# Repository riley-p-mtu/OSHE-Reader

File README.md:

# OSHE-Reader
This project is a work-in-progress in making an open-source E-ink display E-reader. The intention is to read and display EPUB and PDF files, the most popular book formats.

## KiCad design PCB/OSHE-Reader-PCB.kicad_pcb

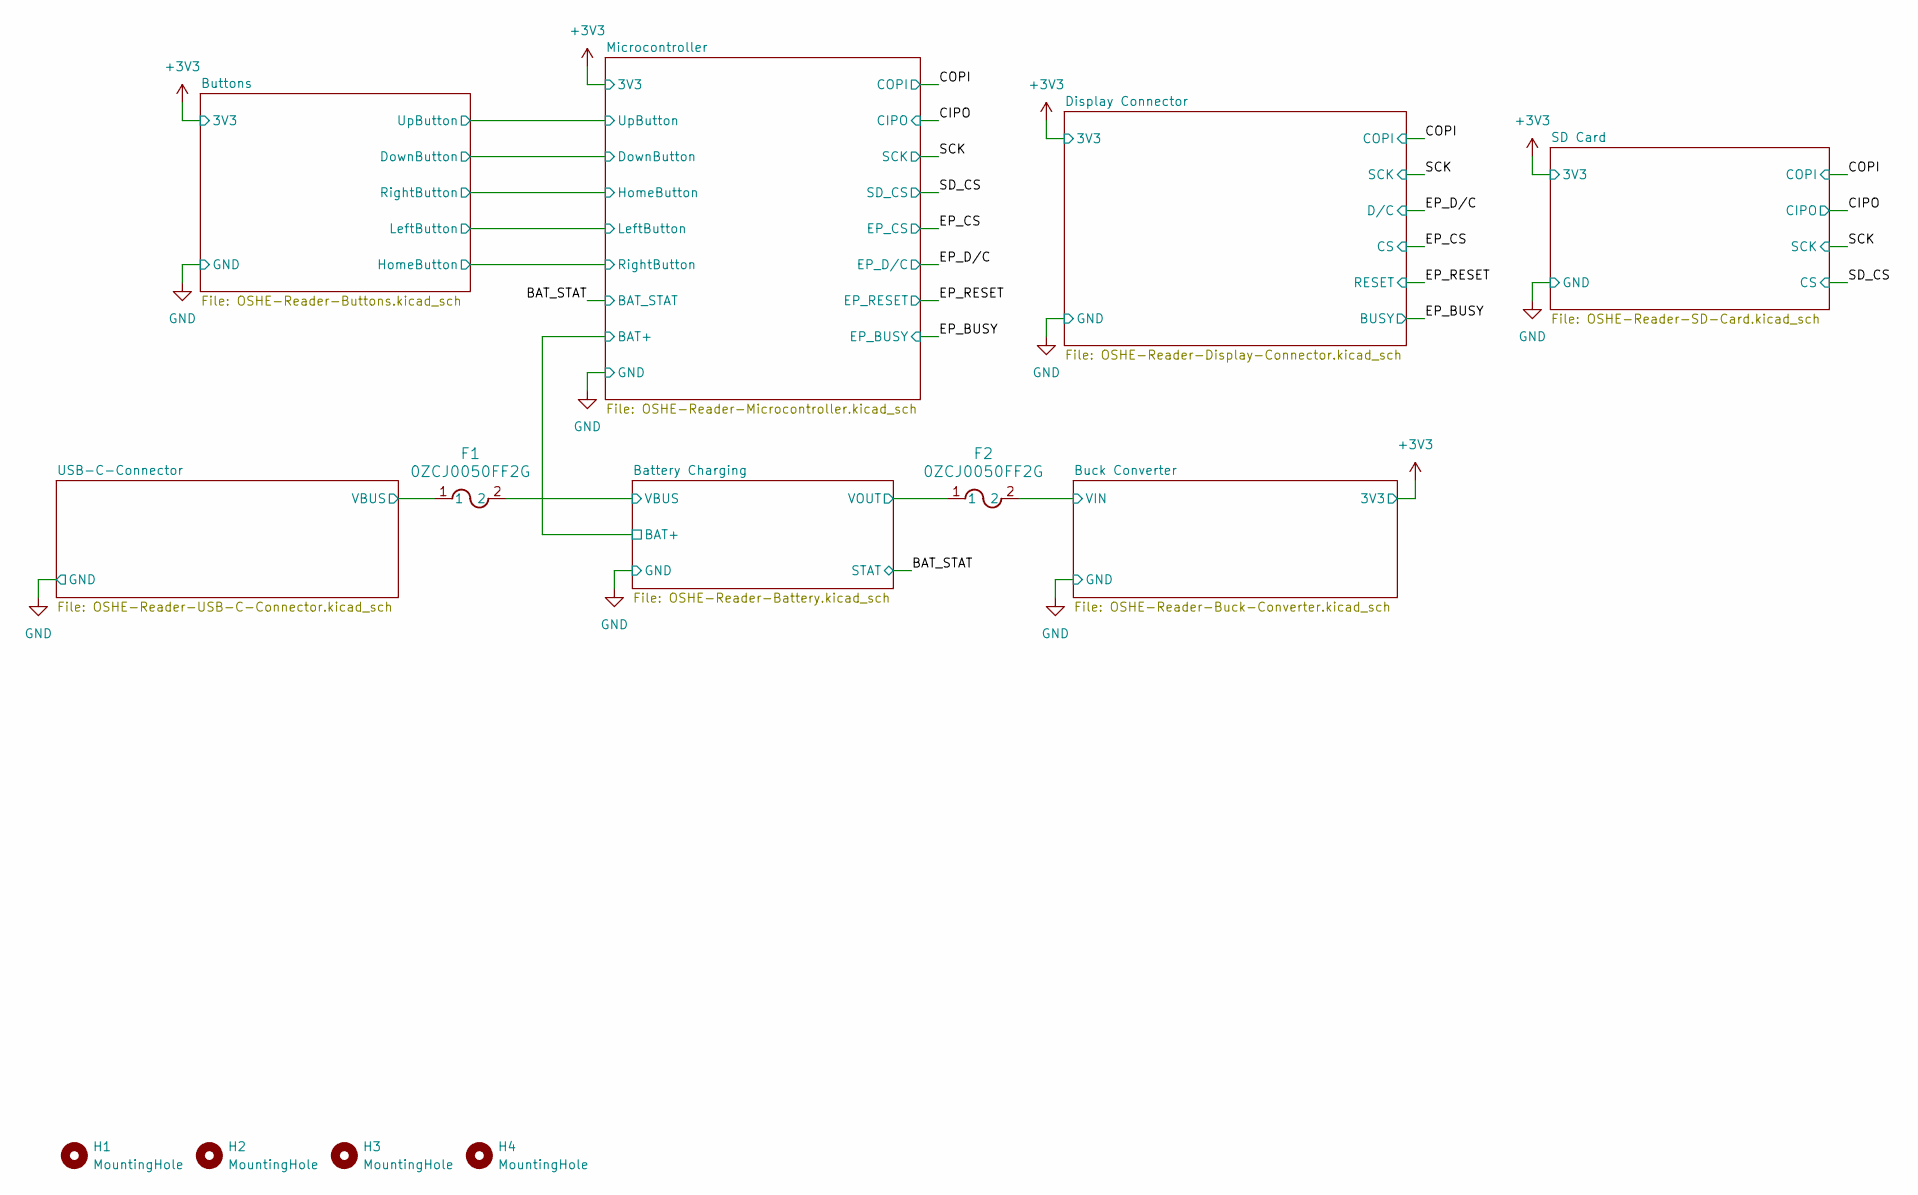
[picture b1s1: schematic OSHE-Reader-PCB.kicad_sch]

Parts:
F1, F2: 0ZCJ0050FF2G; 0ZCJ_BEL
H1, H2, H3, H4: MountingHole; MountingHole_3.2mm_M3

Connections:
/Battery Charging/VBUS: F1.2; also elsewhere on the board
/Battery Charging/VOUT: F2.1; also elsewhere on the board
/Buck Converter/VIN: F2.2; also elsewhere on the board
/USB-C-Connector/VBUS: F1.1; also elsewhere on the board

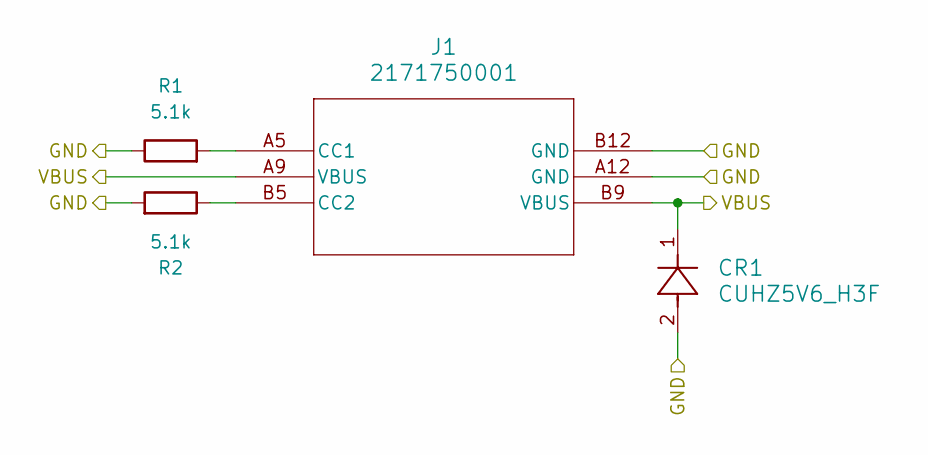
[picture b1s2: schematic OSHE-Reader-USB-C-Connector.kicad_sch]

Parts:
CR1: CUHZ5V6_H3F; SOD-323HEUS2H_TOS
J1: 2171750001; 2171750001_MOL
R1, R2: 5.1k; R_1206_3216Metric

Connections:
/USB-C-Connector/VBUS: CR1.1, J1.A9 (VBUS), J1.B9 (VBUS); also elsewhere on the board
GND: CR1.2, J1.A12 (GND), J1.B12 (GND), R1.1, R2.2; also elsewhere on the board
unnamed: J1.A5 (CC1), R1.2
unnamed: J1.B5 (CC2), R2.1

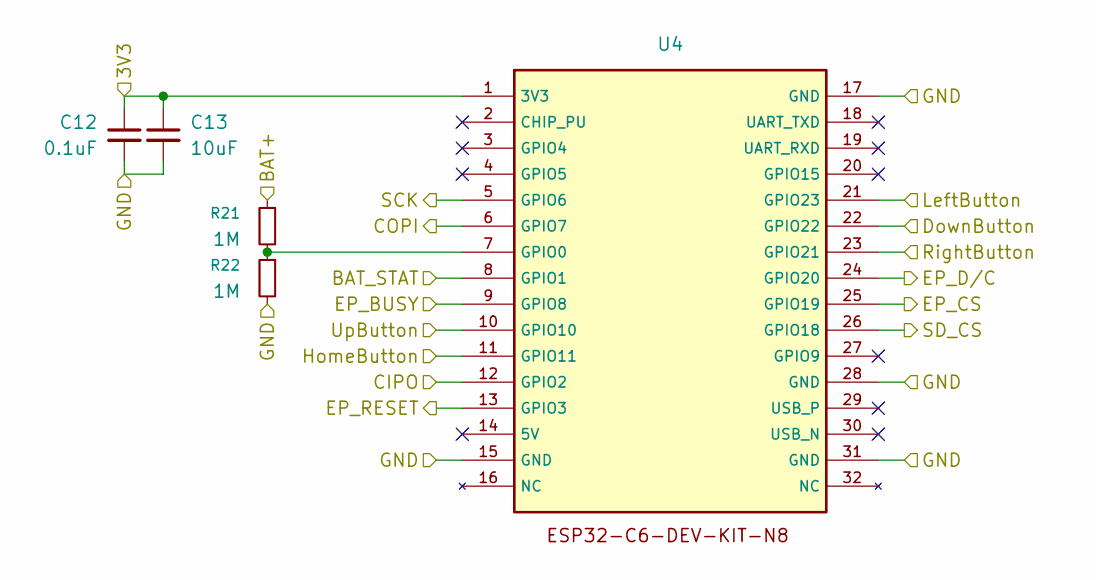
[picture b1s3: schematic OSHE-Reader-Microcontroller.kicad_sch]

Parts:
C12: 0.1uF; C_1206_3216Metric
C13: 10uF; C_1206_3216Metric
R21, R22: 1M; R_1206_3216Metric
U4: ESP32-C6-DEV-KIT-N8

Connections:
+3V3: C12.1, C13.1, U4.1 (3V3); also elsewhere on the board
/BAT_STAT: U4.8 (GPIO1); also elsewhere on the board
/Battery Charging/BAT+: R21.1; also elsewhere on the board
/Buttons/DownButton: U4.22 (GPIO22); also elsewhere on the board
/Buttons/HomeButton: U4.23 (GPIO21); also elsewhere on the board
/Buttons/LeftButton: U4.21 (GPIO23); also elsewhere on the board
/Buttons/RightButton: U4.11 (GPIO11); also elsewhere on the board
/Buttons/UpButton: U4.10 (GPIO10); also elsewhere on the board
/CIPO: U4.12 (GPIO2); also elsewhere on the board
/COPI: U4.6 (GPIO7); also elsewhere on the board
/EP_BUSY: U4.9 (GPIO8); also elsewhere on the board
/EP_CS: U4.25 (GPIO19); also elsewhere on the board
/EP_D/C: U4.24 (GPIO20); also elsewhere on the board
/EP_RESET: U4.13 (GPIO3); also elsewhere on the board
/SCK: U4.5 (GPIO6); also elsewhere on the board
/SD_CS: U4.26 (GPIO18); also elsewhere on the board
GND: C12.2, C13.2, R22.2, U4.15 (GND), U4.17 (GND), U4.28 (GND), U4.31 (GND); also elsewhere on the board
unnamed: R21.2, R22.1, U4.7 (GPIO0)

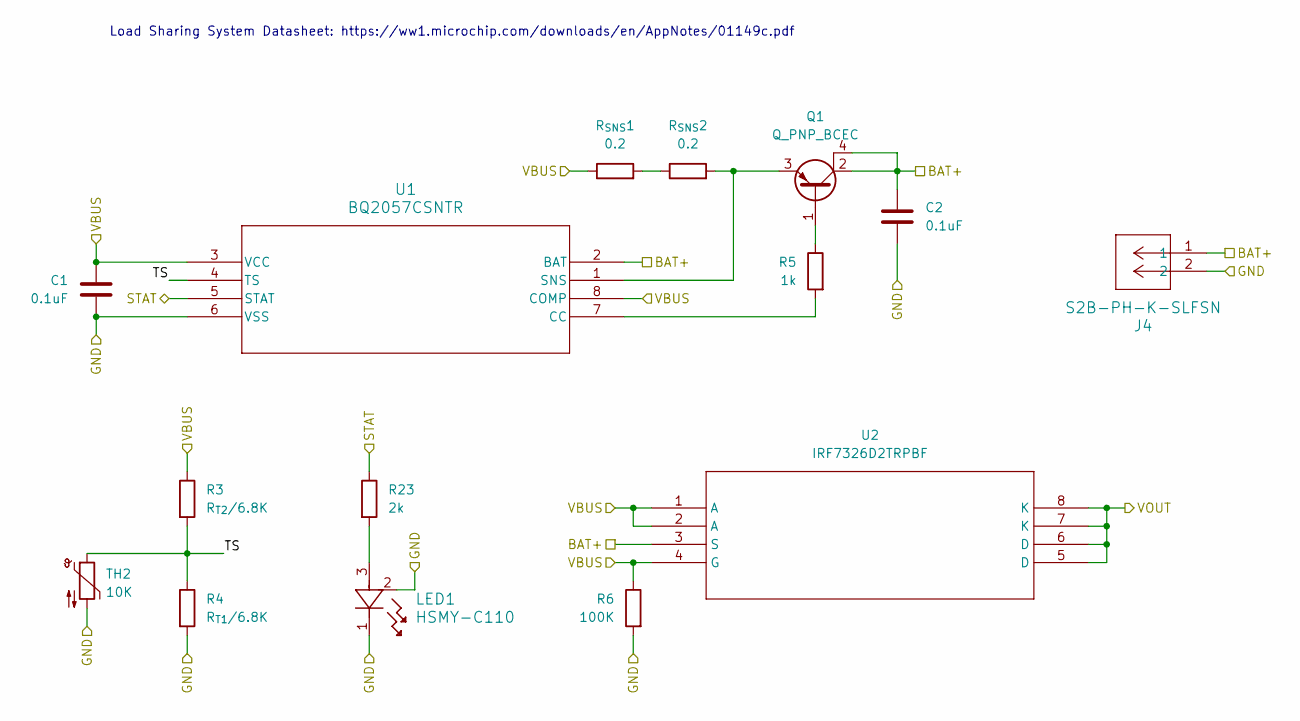
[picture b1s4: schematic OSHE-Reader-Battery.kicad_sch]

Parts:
C1, C2: 0.1uF; C_1206_3216Metric
J4: S2B-PH-K-SLFSN; CONN_S2B-PH-K-S_JST
LED1: HSMY-C110; LED3_HSMx-C110_AVA
Q1: Q_PNP_BCEC; SOT-223
R3: R_{T2}/6.8K; R_1206_3216Metric
R4: R_{T1}/6.8K; R_1206_3216Metric
R5: 1k; R_1206_3216Metric
R6: 100K; R_1206_3216Metric
R23: 2k; R_1206_3216Metric
R_{SNS}1, R_{SNS}2: 0.2; RES_2512_WSL
TH2: 10K; R_Axial_DIN0204_L3.6mm_D1.6mm_P5.08mm_Vertical
U1: BQ2057CSNTR; D8
U2: IRF7326D2TRPBF; SO-8_3.9x4.9mm_P1.27mm

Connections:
/BAT_STAT: R23.1, U1.5 (STAT); also elsewhere on the board
/Battery Charging/BAT+: C2.1, J4.1, Q1.2 (C), Q1.4 (C), U1.2 (BAT), U2.3 (S); also elsewhere on the board
/Battery Charging/TS: R3.2, R4.1, TH2.1, U1.4 (TS)
/Battery Charging/VBUS: C1.1, R3.1, R6.1, R_{SNS}1.1, U1.3 (VCC), U1.8 (COMP), U2.1 (A), U2.2 (A), U2.4 (G); also elsewhere on the board
/Battery Charging/VOUT: U2.5 (D), U2.6 (D), U2.7 (K), U2.8 (K); also elsewhere on the board
GND: C1.2, C2.2, J4.2, LED1.1, LED1.2, R4.2, R6.2, TH2.2, U1.6 (VSS); also elsewhere on the board
unnamed: LED1.3, R23.2
unnamed: Q1.1 (B), R5.1
unnamed: Q1.3 (E), R_{SNS}2.2, U1.1 (SNS)
unnamed: R_{SNS}1.2, R_{SNS}2.1
unnamed: R5.2, U1.7 (CC)

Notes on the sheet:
Load Sharing System Datasheet: https://ww1.microchip.com/downloads/en/AppNotes/01149c.pdf

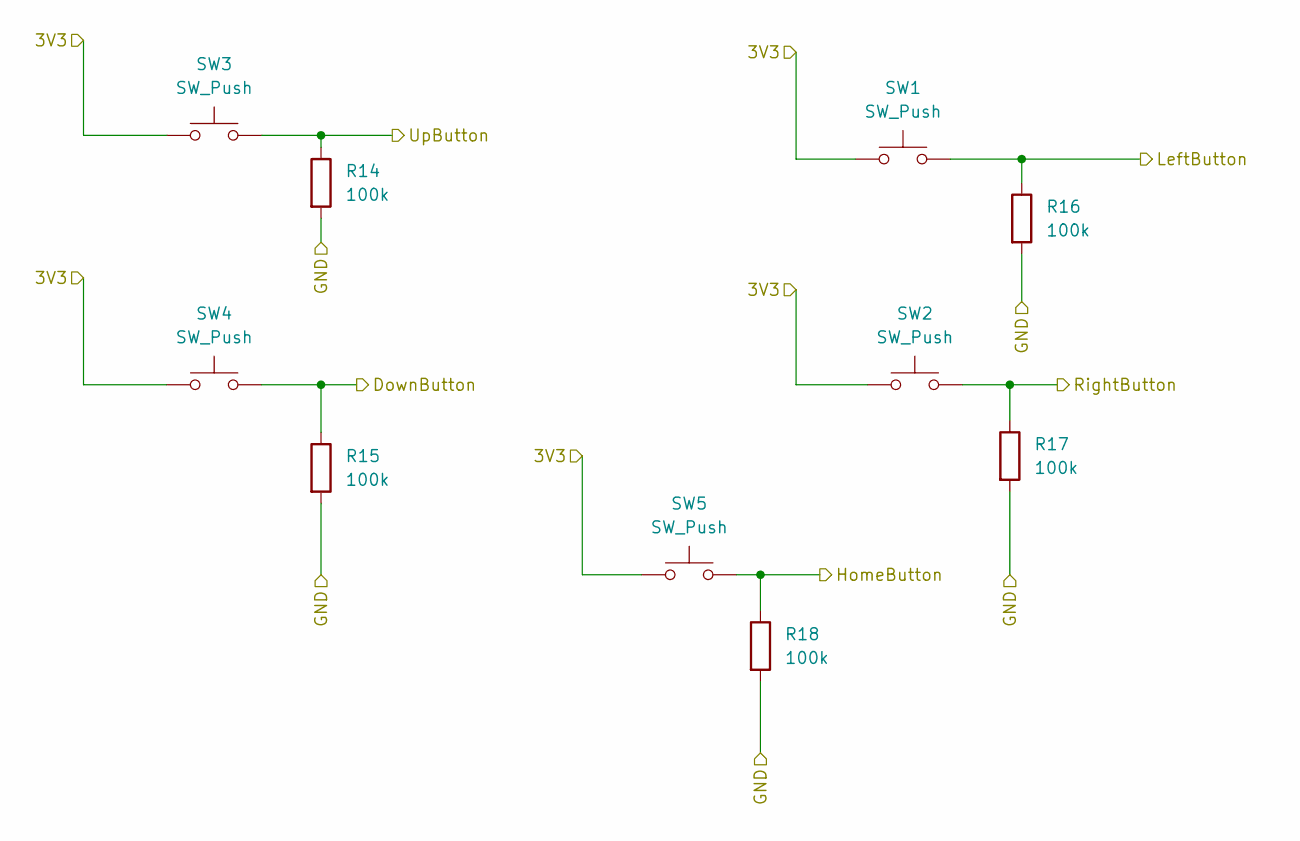
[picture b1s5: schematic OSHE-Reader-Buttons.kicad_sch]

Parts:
R14, R15, R16, R17, R18: 100k; R_1206_3216Metric
SW1, SW2, SW3, SW4, SW5: SW_Push; SW_Tactile_SPST_NO_Straight_CK_PTS636Sx25SMTRLFS

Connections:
+3V3: SW1.2, SW2.1, SW3.1, SW4.1, SW5.1; also elsewhere on the board
/Buttons/DownButton: R15.1, SW4.2; also elsewhere on the board
/Buttons/HomeButton: R18.1, SW5.2; also elsewhere on the board
/Buttons/LeftButton: R16.1, SW1.1; also elsewhere on the board
/Buttons/RightButton: R17.1, SW2.2; also elsewhere on the board
/Buttons/UpButton: R14.1, SW3.2; also elsewhere on the board
GND: R14.2, R15.2, R16.2, R17.2, R18.2; also elsewhere on the board

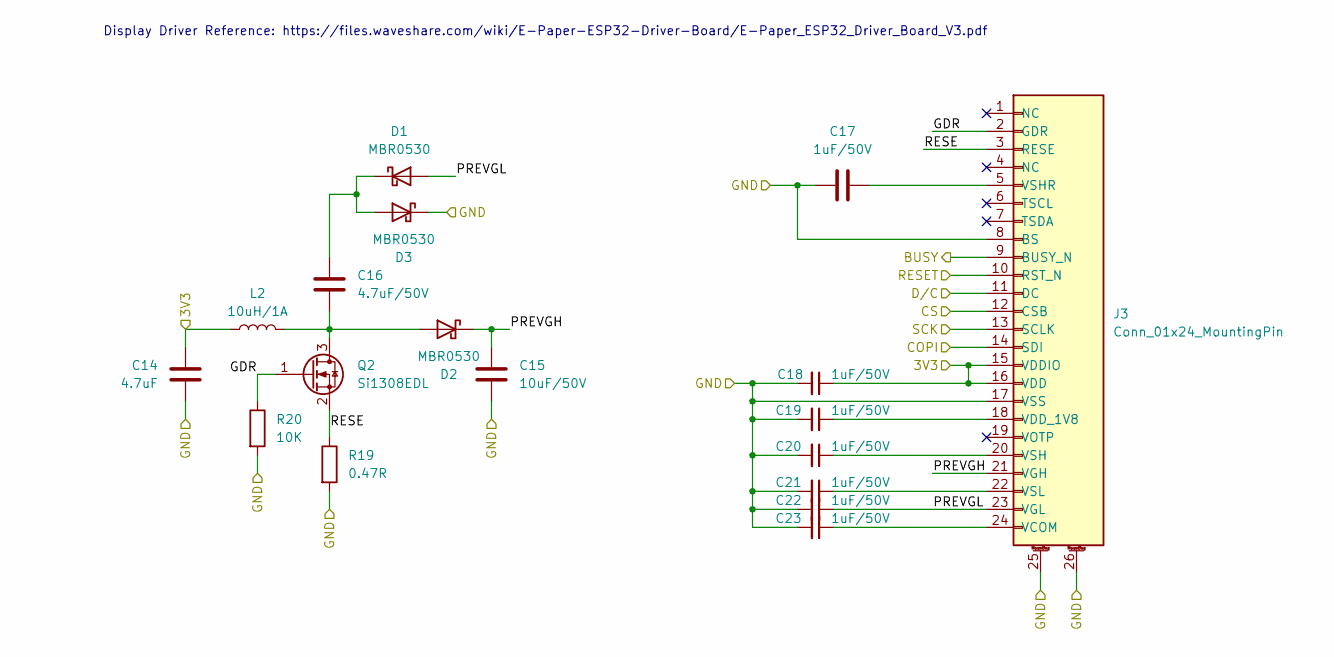
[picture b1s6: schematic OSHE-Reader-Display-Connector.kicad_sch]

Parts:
C14: 4.7uF; C_1206_3216Metric
C15: 10uF/50V; C_1206_3216Metric
C16: 4.7uF/50V; C_1206_3216Metric
C17, C18, C19, C20, C21, C22, C23: 1uF/50V; C_1206_3216Metric
D1, D2, D3: MBR0530; D_SOD-123
J3: Conn_01x24_MountingPin; CONN24_1X24_DRC_FFC_HIR
L2: 10uH/1A; L_1812_4532Metric
Q2: Si1308EDL; SOT-323_SC-70
R19: 0.47R; R_1206_3216Metric
R20: 10K; R_1206_3216Metric

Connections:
+3V3: C14.1, C18.1, J3.15 (VDDIO), J3.16 (VDD), L2.1; also elsewhere on the board
/COPI: J3.14 (SDI); also elsewhere on the board
/Display Connector/GDR: J3.2 (GDR), Q2.1 (G), R20.1
/Display Connector/PREVGH: C15.1, D2.1 (K), J3.21 (VGH)
/Display Connector/PREVGL: C22.1, D1.2 (A), J3.23 (VGL)
/Display Connector/RESE: J3.3 (RESE), Q2.2 (S), R19.1
/EP_BUSY: J3.9 (BUSY_N); also elsewhere on the board
/EP_CS: J3.12 (CSB); also elsewhere on the board
/EP_D/C: J3.11 (DC); also elsewhere on the board
/EP_RESET: J3.10 (RST_N); also elsewhere on the board
/SCK: J3.13 (SCLK); also elsewhere on the board
GND: C14.2, C15.2, C17.2, C18.2, C19.2, C20.2, C21.2, C22.2, C23.2, D3.1 (K), J3.8 (BS), J3.17 (VSS), J3.25, J3.26, R19.2, R20.2; also elsewhere on the board
unnamed: C16.1, D1.1 (K), D3.2 (A)
unnamed: C16.2, D2.2 (A), L2.2, Q2.3 (D)
unnamed: C23.1, J3.24 (VCOM)
unnamed: C19.1, J3.18 (VDD_1V8)
unnamed: C20.1, J3.20 (VSH)
unnamed: C17.1, J3.5 (VSHR)
unnamed: C21.1, J3.22 (VSL)

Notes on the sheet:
Display Driver Reference: https://files.waveshare.com/wiki/E-Paper-ESP32-Driver-Board/E-Paper_ESP32_Driver_Board_V3.pdf

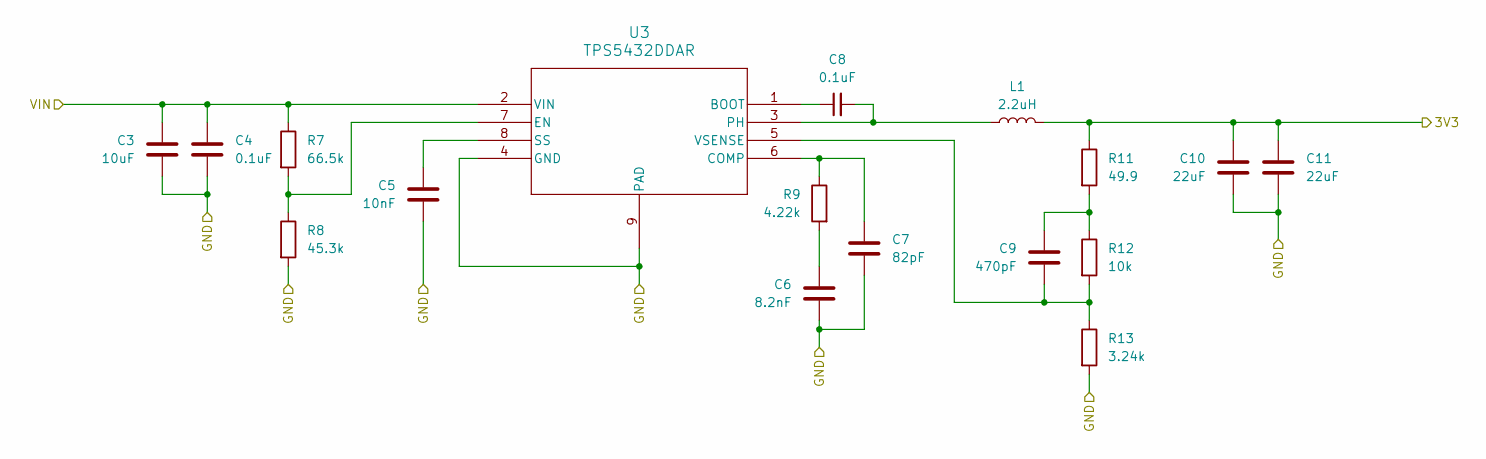
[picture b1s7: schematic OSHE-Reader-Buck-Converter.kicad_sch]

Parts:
C3: 10uF; C_1206_3216Metric
C4, C8: 0.1uF; C_1206_3216Metric
C5: 10nF; C_1206_3216Metric
C6: 8.2nF; C_1206_3216Metric
C7: 82pF; C_1206_3216Metric
C9: 470pF; C_1206_3216Metric
C10, C11: 22uF; C_1206_3216Metric
L1: 2.2uH; L_1206_3216Metric
R7: 66.5k; R_1206_3216Metric
R8: 45.3k; R_1206_3216Metric
R9: 4.22k; R_1206_3216Metric
R11: 49.9; R_1206_3216Metric
R12: 10k; R_1206_3216Metric
R13: 3.24k; R_1206_3216Metric
U3: TPS5432DDAR; DDA_R-PDSO-G8_TEX

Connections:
+3V3: C10.2, C11.2, L1.2, R11.1; also elsewhere on the board
/Buck Converter/VIN: C3.1, C4.1, R7.1, U3.2 (VIN); also elsewhere on the board
GND: C3.2, C4.2, C5.2, C6.2, C7.2, C10.1, C11.1, R8.2, R13.2, U3.4 (GND), U3.9 (PAD); also elsewhere on the board
unnamed: C6.1, R9.2
unnamed: C9.2, R11.2, R12.1
unnamed: C8.1, U3.1 (BOOT)
unnamed: C7.1, R9.1, U3.6 (COMP)
unnamed: R7.2, R8.1, U3.7 (EN)
unnamed: C8.2, L1.1, U3.3 (PH)
unnamed: C5.1, U3.8 (SS)
unnamed: C9.1, R12.2, R13.1, U3.5 (VSENSE)

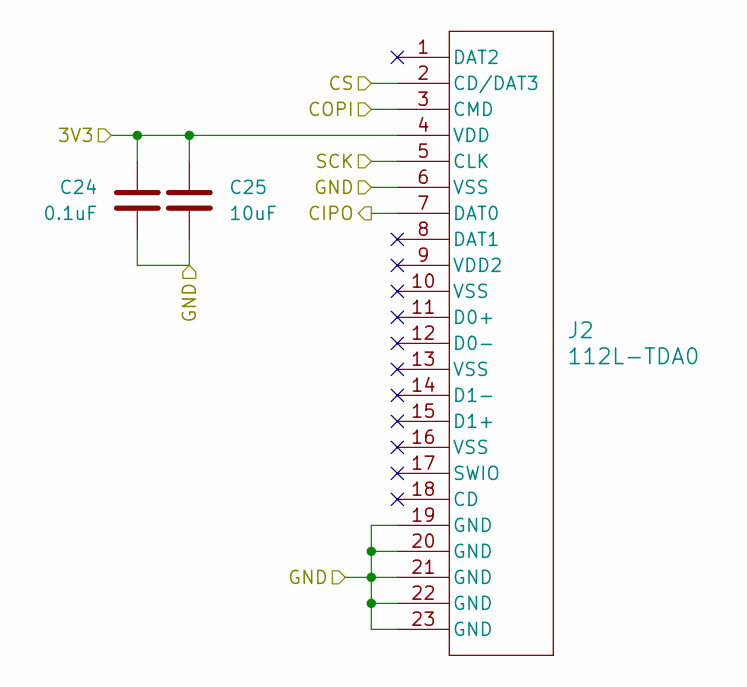
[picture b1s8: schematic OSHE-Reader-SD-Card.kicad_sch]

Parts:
C24: 0.1uF; C_1206_3216Metric
C25: 10uF; C_1206_3216Metric
J2: 112L-TDA0; CONN_112L-TDA0_ATT

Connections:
+3V3: C24.1, C25.1, J2.4 (VDD); also elsewhere on the board
/CIPO: J2.7 (DAT0); also elsewhere on the board
/COPI: J2.3 (CMD); also elsewhere on the board
/SCK: J2.5 (CLK); also elsewhere on the board
/SD_CS: J2.2 (CD/DAT3); also elsewhere on the board
GND: C24.2, C25.2, J2.6 (VSS), J2.19 (GND), J2.20 (GND), J2.21 (GND), J2.22 (GND), J2.23 (GND); also elsewhere on the board

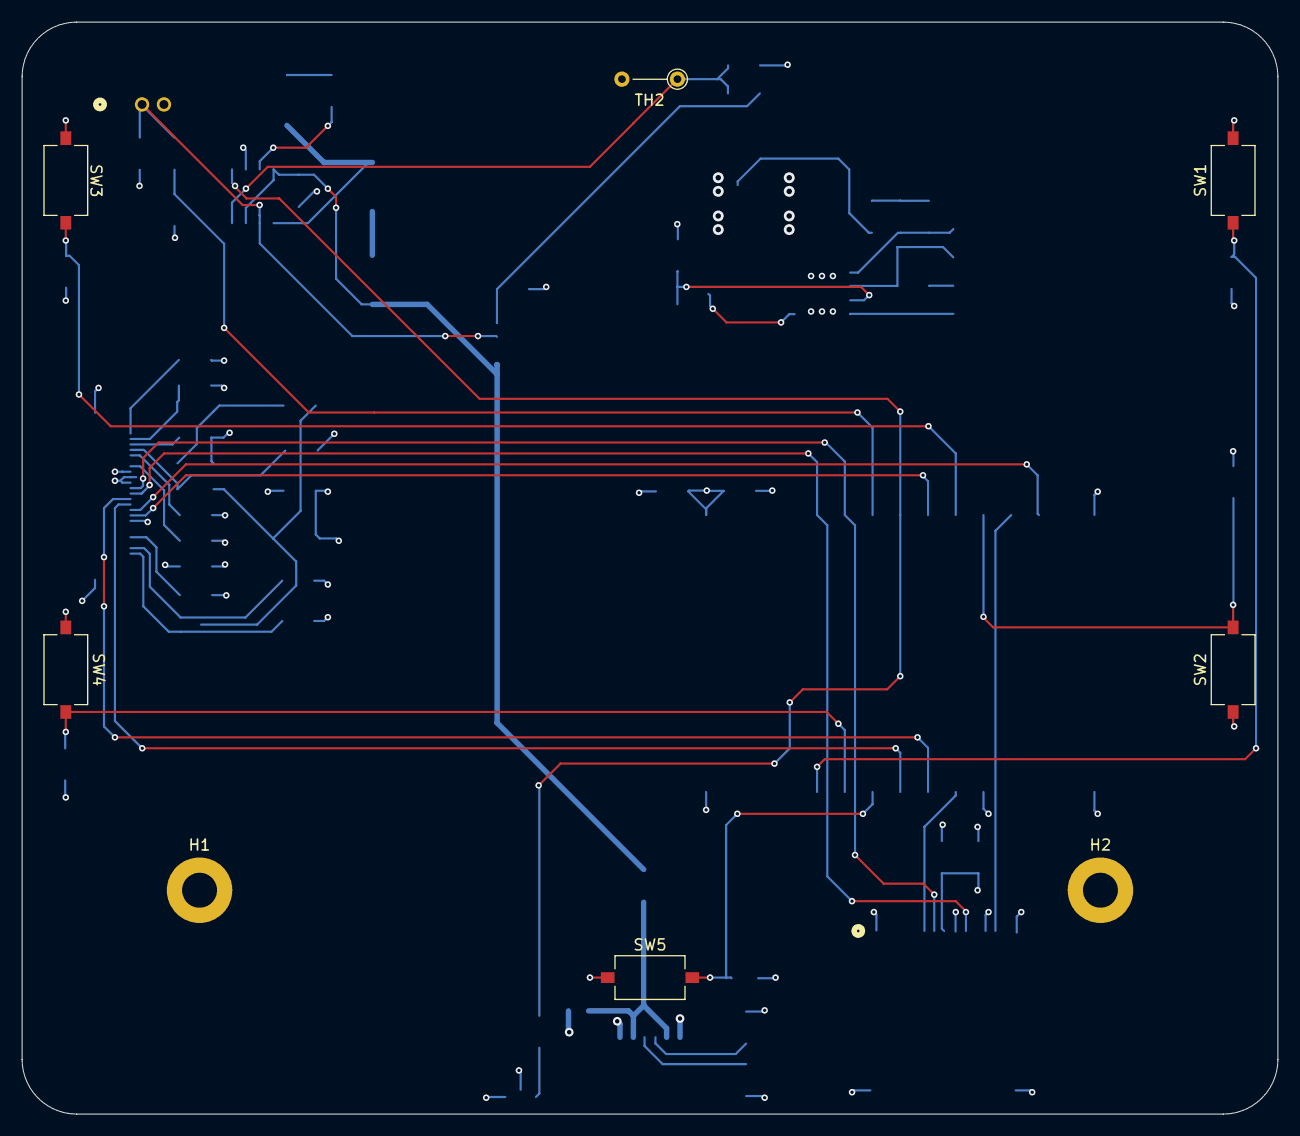
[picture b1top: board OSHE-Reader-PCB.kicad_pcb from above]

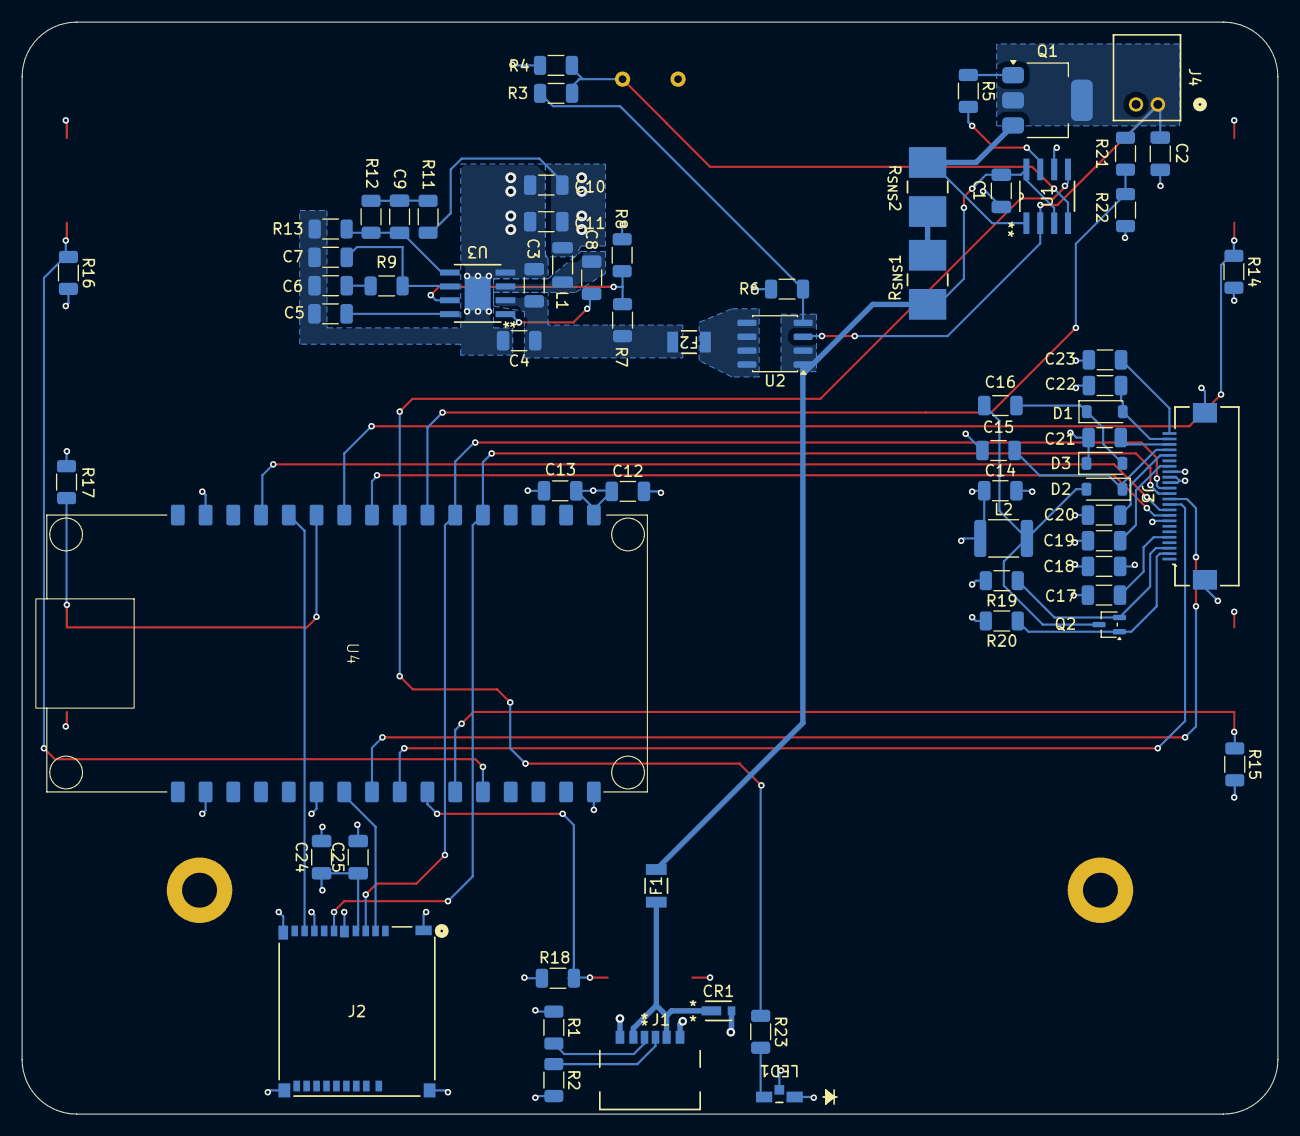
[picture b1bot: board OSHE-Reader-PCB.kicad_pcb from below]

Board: 4 copper layers, 115.0 x 100.0 mm, 78 parts (68 on the bottom side), 49 nets.

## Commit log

2025-09-10 started pcb project and imported footprint for MCP73837 battery charging IC
2025-09-10 added charging IC to schematic :)
2025-09-10 added .lck files to gitignore
2025-09-14 Added battery charging and power selector circuit to schematic, added symbols and footprints for BQ2057CSNTR, removed symbols and footprints for unused MCP73837T
2025-09-17 relabeled groups, added indicator LED
2025-09-18 split pcb up into hierarchical files, playing with power flags and ERC
2025-09-18 changed sheet name from Battery to Battery-Charger
2025-09-18 added VBUS port on battery-charger section
2025-09-20 Started work to unzip epub
    Minizip is a library I am trying to use for unzipping the epub and getting the content file, which will let us identify the title, files containing pages, and the reading order of those pages. Once w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
2025-09-26 Added Buck Converter to Schematic.
    added buck converter, and hooked it up. In theroy should work from, 3.7-3.5 volts inputed, and output 3.3 volts
2025-09-27 Added LVGL files for GUI
2025-09-28 added waveshare e-paper firmware example, NOTE: need to install the waveshare board library, see https://www.waveshare.com/wiki/E-Paper_ESP32_Driver_Board#Preparation
2025-09-28 refactored battery charger, added usb-c port sheet
2025-10-01 added sd card test firmware with correct pins
2025-10-02 Update README.md
    Providing more info on how to actually run the program, as well as more links for the libraries
2025-10-02 Update Parsing.c
    Added XML parsing functionality, currently just printing checks while going through content.opf. While looking for XML libraries I found expat, but we could still use whatever. Also updated some vari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
2025-10-02 Create expat.h
    I am not actually sure this file is required with the setup I gave in the README, but I have it in my folder and I don't want to break anything
2025-10-02 Buck converter added
    added the buck converter
2025-10-02 Starting GUI development :)
2025-10-03 minor changes to osh logo in battery charger
2025-10-06 Update home.xml
    Added some buttons and text to the home screen. I am still figuring out how to manipulate the font size and overall we should take a look at UI design principles so we can be consistent in button siz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
2025-10-09 Changed home screen and began settings screen
    Added a few fonts to the globals file for title and other text size. I have been following the LVGL pro documentation
2025-10-10 created symbol for Co-packaged PMOS and Schottky Diode
2025-10-10 renamed buck converter hierarchical sheet
2025-10-10 updated battery charging and overall sheet with new mosfet + diode symbol
2025-10-10 added symbol footprints and block libs for buck converter and TVS diode
2025-10-10 maybe finished usbc connector, depends on if we want to read CC lines for power adjustment
2025-10-10 added hierarchical symbols to Buck, and did miscelaneous fixes
2025-10-12 made symbol and footprint for waveshare ESP32-C6
2025-10-12 fixed up the pcb so everything is *basically* passing ERC
2025-10-12 placed hierarchical sheets for other schematic components, TODO: the rest
2025-10-21 added micro sd card reader kicad lib
2025-10-21 started work adding hierarchical power pins to mcu and sd card sheets
2025-10-22 work on pcb, adjusted components and started building ribbon connector for display
2025-10-22 added ribbon connector symbol (really bad), footprint, and 3d model, updated custom symbol with two mounting points on pins 25 and 26
2025-10-23 added symbol footprint and model for current sense resistor in battery charger
2025-10-23 added footprint to connector in schematic
2025-10-23 added usbc connector symbol, footprint, and model, updated symbol in schematic
2025-10-23 misc work on schematic
2025-10-23 unzipped moby dick so we can play with the raw files
2025-10-24 fixed mislabeling of pins on battery charging IC
2025-10-30 minor fixes to hierarchical aspects of sheet + slight progress on display connector
2025-10-30 sd card *should* be done with the exception of things like decoupling caps
2025-10-30 added decoupling cap to sd card socket
2025-10-30 put 3v3 on high side of buttons instead of hierarchical pins
2025-10-30 oops forgot to update sheet pins
2025-10-30 hopefully finshed buttons?
2025-10-30 sheet pins for SD card module
2025-10-30 Arduino SD Read and Micro Input
2025-10-30 Updates reader display connector
2025-11-01 Updating pins in roots file
2025-11-04 removed .DS_Store files and updated gitignore
2025-11-04 updated sd card main sheet pins, swapped big caps for small ones on display connector for better readability
2025-11-04 cleaned up main sheet and synced labels for presentation
2025-11-06 added EPD-Example for displaying OSHE Logo
2025-11-06 HOPEFULLY GOOD FOR EVER (good for first semester) :)
2025-11-06 small
2025-11-09 Major Updates to every screen in UI
2025-11-09 Started getting button input to work with directories
2025-11-09 changed pins for buttons
2025-11-09 fixed components dissapearing after reversion from breaking commit
2025-11-10 Updated UI slightly
    Added more to brightness section in settings, can fix the spacing issues if it is a problem
2025-11-10 added code to prevent repeating button presses
2025-11-10 Added events to home screen, & majorly updated epub parser
2025-11-10 Fixed typos in parsing file
2026-01-10 Create LICENSE
2026-01-16 fixed battery voltage input to mcu being over 3.3V, minor changes to layout of sd card schematic
2026-01-16 added resettable fuse to libs
2026-01-16 resettable fuse symbol, footprint, and 3d model
2026-01-16 added fuses to schematic, updated pcb with new components
2026-01-30 Update OSHE-Reader-PCB.kicad_pcb
    Added resistor footprint
2026-01-30 removed old battery and thermistor references
2026-01-30 Update OSHE-Reader-Battery.kicad_sch
    changing resistor value for the thermstor
2026-01-30 Added LED to battery charger
2026-01-30 Footprint assignments
    Added more footprints
2026-01-31 Footprints added
    All footprints added (problem with J1 for some reason) ((pads of the display driver))
2026-01-31 PCB Work
    Fiddled with PCB :/
2026-01-31 PCB
    PCB
2026-02-01 Did a bunch of work with final preparations of the schematic for pcb routing
2026-02-02 Adding v1 case files
    WIP
2026-02-02 Added edge cuts with proper sizing for case, and properly positioned mounting holes for case, started positioning larger components
2026-02-03 PCB Update
    updated PCB with dimensions and took notes on said dimensions based on case CAD model
2026-02-03 shortened pcb to make room for battery and started laying out components
2026-02-03 Definative PCB edge cuts
2026-02-03 Fixed some items being connected to +3V3 and some to +3.3V
2026-02-03 Made updates when Ian wasn't looking
    PCB changes (slight, changes sizes of mounting holes to fit
2026-02-06 Started routing PCB & added case dxf for reference
2026-02-06 Created LVGL Config File
    Config for using LVGL, settings should be correct for what we are doing. Include this right in the Libraries folder in the Arduino IDE
2026-02-06 Added button init
2026-02-06 More work done on PCB. TODO: Battery Charging and Buck Converter
2026-02-09 Updated PCB
    Did some work on the PCB, placing footprints
2026-02-10 Re-did buck converter schematic sheet to more closely resemble TI's datasheet, implemented buck converter on PCB following TI's datasheet layout example
2026-02-10 PCB Update
    updated some PCB traces
2026-02-10 PCB Update
    Updated the PCB
2026-02-11 Updated footprint to prevent overlapping soldermask and silkscreen around pads
2026-02-11 Finished main draft of PCB, TODO: OSHE logo, Peer review
